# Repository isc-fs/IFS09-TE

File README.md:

# IFS09-TE

Hardware design, embedded firmware, and real-time telemetry software for the **Telemetry & Data Acquisition Subsystem** of the **IFS09**, developed for the **ISC Formula Student Racing Team** (Season 2026/2027).

---

## Subsystem Architecture

```
+-----------------------------------------------------------------------------------------+
|                                     IFS09 RACE CAR                                      |
|  [Sensors & CAN Bus] ---> [ECU / VCU] ---> [Telemetry TX: nRF24L01+ PA+LNA]            |
+---------------------------------------------------+-------------------------------------+
                                                    |
                                             2.4 GHz RF Link
                                        (Trackside Line-of-Sight)
                                                    |
+---------------------------------------------------v-------------------------------------+
|                         IFS09 TELEMETRY RECEIVER (BASE STATION)                         |
|                                                                                         |
|  [External 2.4GHz Antenna] ===> [SMA Jack] ===> [nRF24L01+ PA+LNA Module]               |
|                                                        |                                |
|                                                    SPI Bus                              |
|                                                        v                                |
|                                              [Arduino Nano 3.0]                         |
|                                                 (ATmega328P)                            |
|                                                        |                                |
|                                              USB-C Serial (115200)                      |
|                                                        v                                |
|                                    [Ground Station: isc_realtime_26]                    |
+-----------------------------------------------------------------------------------------+
```

---

## Repository Structure

```
IFS09-TE/
+-- .github/workflows/          # Team automation workflows (issue tracking, roadmap, CI)
+-- isc_realtime_26/            # Real-time telemetry monitoring GUI & data acquisition
¦   +-- ui.py                   # Main PyQt5 dashboard & diagnostics UI
¦   +-- ISC_RTT_serial.py       # Serial communication, framing & packet decoding
¦   +-- ISC_RTT_demo.py         # Offline simulation / bench demo generator
¦   +-- isc_marple.py           # Real-time cloud sync with Marple analytics
¦   +-- ISC_RTT.spec            # PyInstaller distribution build specification
¦   +-- docs / guides           # Guides and Work Orders (Word/PDF)
+-- firmware/                   # Embedded firmware
¦   +-- RTT_nano_26/            # Current Season 09 Telemetry Receiver Arduino firmware
¦   +-- RTT_nano/               # Historical receiver firmware & high-range variants
¦   +-- nrf24/                  # STM32 transmitter firmware for telemetry radio node
+-- hardware/                   # Hardware EDA projects & documentation
¦   +-- IFS09-TeleReceiver/     # KiCad PCB project, schematics, layout, and production files
¦   +-- docs/                   # Block diagrams, pinout diagrams, 3D PCB renders
¦   +-- *.pdf                   # Schematics (v1.0 & v2.0), Design Reports, and Work Orders
+-- ROADMAP.md                  # Telemetry subsystem season roadmap & milestones
+-- README.md                   # This documentation
```

---

## Getting started

1. Create a GitHub account if you don't have one yet.
2. Download and install [GitHub Desktop](https://desktop.github.com/) (beginner) or [Git CLI](https://git-scm.com/book/en/v2/Getting-Started-Installing-Git) (advanced).
   - If this is your first time using GitHub Desktop, make sure to read the [User Manual](https://help.github.com/desktop/guides/).
   - If this is your first time using Git, start with a tutorial:
     - [Git Tutorial](https://git-scm.com/docs/gittutorial)
     - [Atlassian Git Tutorial](https://www.atlassian.com/git/tutorials/)
   - Keep a copy of [GitHub's Git Cheat Sheet](https://services.github.com/kit/downloads/github-git-cheat-sheet.pdf) handy as a reference.

3. Clone this repository to your machine:
   - **SSH:** `git@github.com:isc-fs/IFS09-TE.git`
   - **HTTPS:** `https://github.com/isc-fs/IFS09-TE.git`

---

## Running the Real-Time Telemetry Software (`isc_realtime_26`)

### Requirements
- Python 3.11+
- Virtual environment recommended:

```bash
cd isc_realtime_26
python -m venv .venv
# Windows:
.venv\Scripts\activate
# Linux/macOS:
source .venv/bin/activate

pip install --upgrade pip
pip install pyinstaller pyqt5 matplotlib numpy pyserial requests openpyxl influxdb-client pandas marpledata
```

### Launching the Dashboard
- **Live vehicle / bench mode:**
  ```bash
  python ui.py
  ```
- **Demo / simulation mode:**
  ```bash
  python ISC_RTT_demo.py
  ```

---

## How we work with this repository

### Main branches

The repository follows standard ISC branching rules:

- **`main`** is the production branch. It contains only validated code, schematics, and firmware ready for track operations. Never work directly on it.
- **`dev`** is the development branch. It is the integration point where everyone's work comes together. Never work directly on it either  all changes arrive through a feature branch.

```
main  ------------------?----------------------?--?  (validated releases only)
                        ?                      ?
dev   ------?---?---?---?---?---?---?---?---?--?--?  (continuous integration)
            ?   ?       ?   ?   ?       ?   ?
          feat/1 fix/1 feat/2 fix/2   feat/3 fix/3
```

### Feature branches

All work  whether a new feature or a bug fix  is done on a **feature branch** created from `dev`. When the work is ready, a Pull Request is opened toward `dev`, reviewed, merged, and the branch is deleted.

There are two branch types, each with its own independent numeric counter:

```
feat/<n>   ?  new functionality  (feat/1, feat/2, feat/3 ...)
fix/<n>    ?  bug fix            (fix/1,  fix/2,  fix/3  ...)
```

The `feat` and `fix` counters are independent: `feat/2` and `fix/2` can exist at the same time with no conflict.

### Tracking branch history

Feature branches are deleted after merging to keep the repository clean. The history of each branch is preserved in **GitHub Issues**.

Every branch has one associated issue. The issue carries a **label** (`feat` or `fix`) and its title includes the branch number, for example: `[feat/3] Add CAN broadcast for mission state`. When the branch is merged and deleted, the issue is closed  becoming a permanent record of all the work done.

---

## Automation

The repository includes GitHub Actions workflows that manage tracking issues automatically. No setup is required  it works for every developer as soon as they create a branch.

- **Automatic issue creation:** When a `feat/*` or `fix/*` branch is pushed, an issue is opened with template sections and assigned labels.
- **Wrong number warning:** Validates that branch numbering increments monotonically.
- **Auto-fill description:** The first commit message automatically populates the issue description.
- **Roadmap synchronization:** Updates subsystem progress in `ROADMAP.md`.

---

## Step-by-step workflow

1. **Create the branch:**
   ```bash
   git checkout dev
   git pull origin dev
   git checkout -b feat/1    # or fix/1
   ```
2. **Push the branch:**
   ```bash
   git push origin feat/1
   ```
   The tracking issue will be opened automatically on GitHub.

3. **Work and commit:**
   ```bash
   git add .
   git commit -m "feat(telemetry): describe your changes clearly"
   git push origin feat/1
   ```

4. **Open a Pull Request:**
   Target `dev`, write `Closes #<issue-number>` in the description, verify no errors, and request subsystem review.

---

*ISC Racing Team  IFS09*

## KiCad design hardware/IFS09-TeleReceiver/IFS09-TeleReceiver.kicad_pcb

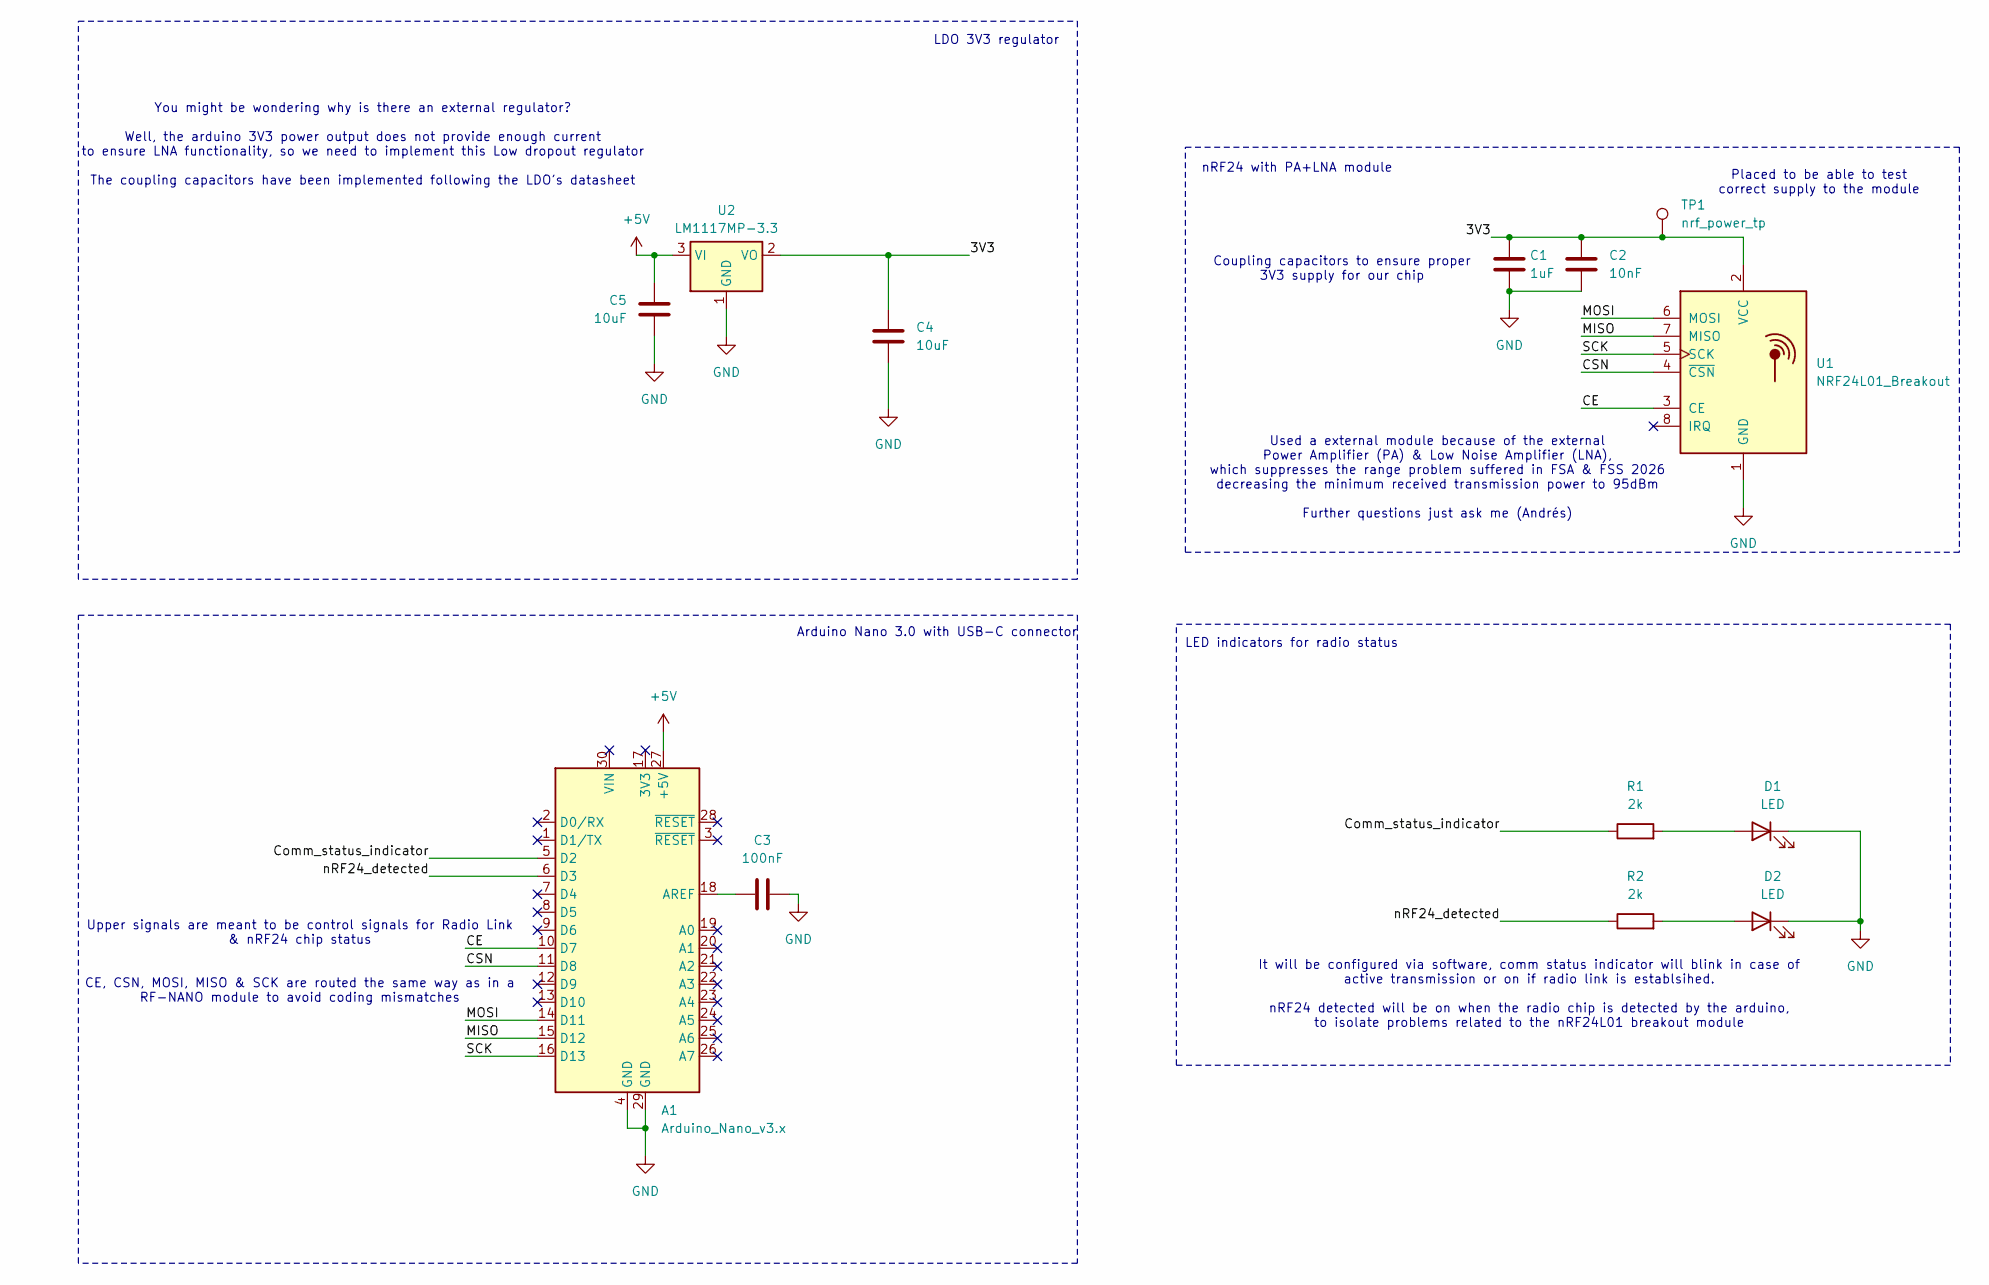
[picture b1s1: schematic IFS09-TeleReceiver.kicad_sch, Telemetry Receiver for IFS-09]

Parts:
A1: Arduino_Nano_v3.x; Arduino_Nano_WithMountingHoles
C1: 1uF; C_0805_2012Metric_Pad1.18x1.45mm_HandSolder
C2: 10nF; C_0805_2012Metric_Pad1.18x1.45mm_HandSolder
C3: 100nF; C_0805_2012Metric_Pad1.18x1.45mm_HandSolder
C4, C5: 10uF; C_0805_2012Metric_Pad1.18x1.45mm_HandSolder
D1, D2: LED; LED_0805_2012Metric_Pad1.15x1.40mm_HandSolder
R1, R2: 2k; R_0805_2012Metric_Pad1.20x1.40mm_HandSolder
TP1: nrf_power_tp; TestPoint_Pad_D2.0mm
U1: NRF24L01_Breakout; nRF24L01_Breakout
U2: LM1117MP-3.3; SOT-223-3_TabPin2

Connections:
+5V: A1.27 (+5V), C5.1, U2.3 (VI)
/3V3: C1.2, C2.2, C4.1, TP1.1 (1_1), U1.2 (VCC), U2.2 (VO)
/CE: A1.10 (D7), U1.3 (CE)
/CSN: A1.11 (D8), U1.4 (~CSN)
/Comm_status_indicator: A1.5 (D2), R1.1
/MISO: A1.15 (D12), U1.7 (MISO)
/MOSI: A1.14 (D11), U1.6 (MOSI)
/SCK: A1.16 (D13), U1.5 (SCK)
/nRF24_detected: A1.6 (D3), R2.1
GND: A1.4 (GND), A1.29 (GND), C1.1, C2.1, C3.1, C4.2, C5.2, D1.1 (K), D2.1 (K), U1.1 (GND), U2.1 (GND)
unnamed: A1.18 (AREF), C3.2
unnamed: D1.2 (A), R1.2
unnamed: D2.2 (A), R2.2

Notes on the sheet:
You might be wondering why is there an external regulator? Well, the arduino 3V3 power output does not provide enough current to ensure LNA functionality, so we need to implement this Low dropout regulator The coupling capacitors have been implemented following the LDO's datasheet
LDO 3V3 regulator
nRF24 with PA+LNA module
LED indicators for radio status
It will be configured via software, comm status indicator will blink in case of active transmission or on if radio link is establsihed. nRF24 detected will be on when the radio chip is detected by the arduino, to isolate problems related to the nRF24L01 breakout module
Placed to be able to test correct supply to the module
Coupling capacitors to ensure proper 3V3 supply for our chip
Arduino Nano 3.0 with USB-C connector
Used a external module because of the external Power Amplifier (PA) & Low Noise Amplifier (LNA), which suppresses the range problem suffered in FSA & FSS 2026 decreasing the minimum received transmission power to 95dBm Further questions just ask me (Andrés)
Upper signals are meant to be control signals for Radio Link & nRF24 chip status CE, CSN, MOSI, MISO & SCK are routed the same way as in a RF-NANO module to avoid coding mismatches

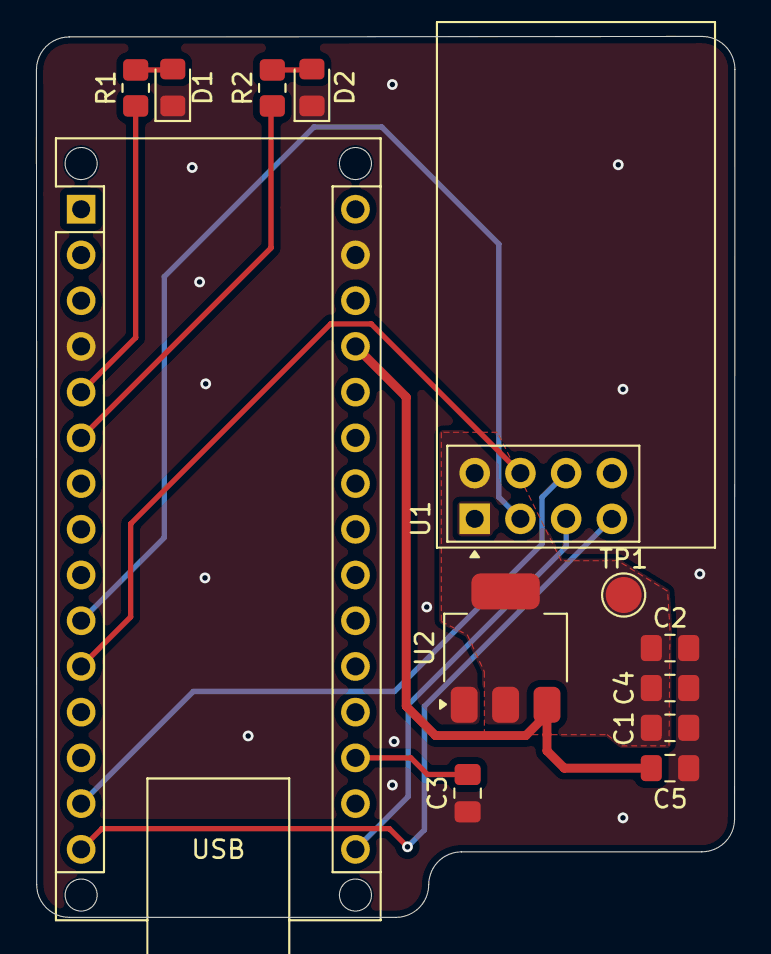
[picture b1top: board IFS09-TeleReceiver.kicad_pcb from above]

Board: 2 copper layers, 38.8 x 48.9 mm, 13 parts (0 on the bottom side), 13 nets.
